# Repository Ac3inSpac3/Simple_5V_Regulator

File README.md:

# Basic 5V Regulator for Raspberry Pi

## Introduction

This 5V regulator was designed for my EGH419 Class (Mechatronics design 3). It was designed to take the high input voltage the main robot ran off, (a 6s Li-Po drone battery or 4 individual 18650 cells in parallel) and output a consistent 5V for the raspberry pi to run off. The regulator needed to be capable of providing enough current for the Pi to run OpenCV object recognition on top of the navigation code. 

## Features

- Input Voltage: 30V (maximum)
- Output Voltage: 5V
- High Current Output

## Schematic
The schematic for this PCB was designed in KiCAD. KiCAD was used because it is a free program and I do not need to mess around with Educational Licences like I did when working in Altium.
A fuse was implemented into the schematic; however, it was not placed when the PCB was assembled.

## PCB
The PCB was designed and sent to JLCPCB to be manufactured (Manufacturing and Gerber files provided).

## Final Product
With the PCB now manufactured it was tested and placed into the robot. It worked well, providing 5V to the Raspberry Pi without any annoying low power warnings like the previous solution had done.

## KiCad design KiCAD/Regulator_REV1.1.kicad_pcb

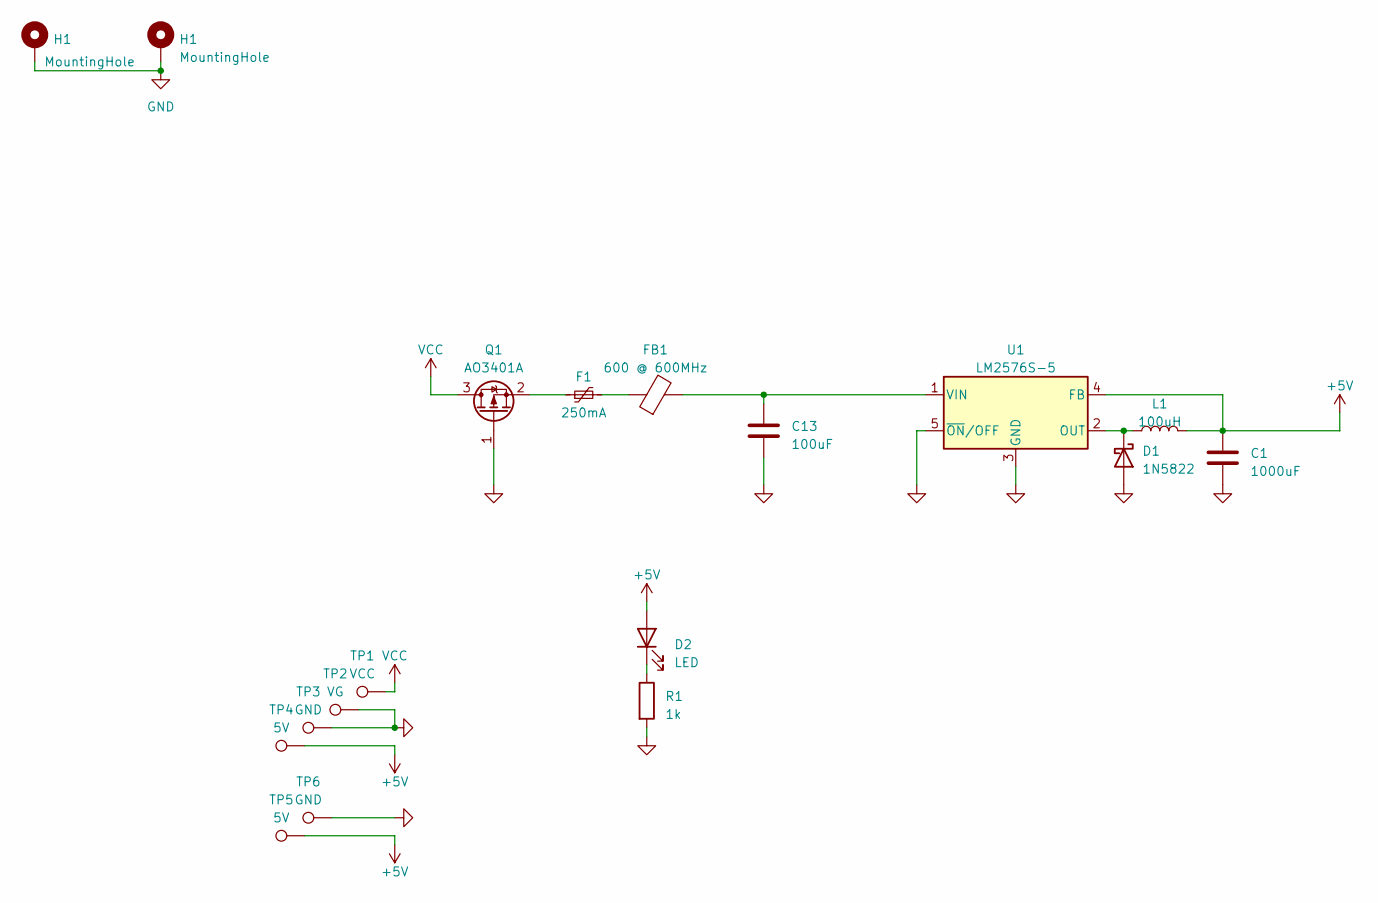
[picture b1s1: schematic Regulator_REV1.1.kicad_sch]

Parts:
C1: 1000uF; C_Elec_10x10.2
C13: 100uF; C_1206_3216Metric
D1: 1N5822; D_DO-201AD_P15.24mm_Horizontal
D2: LED; LED_0603_1608Metric
F1: 250mA; Fuse_1206_3216Metric
FB1: 600 @ 600MHz; L_0805_2012Metric
H1: MountingHole; MountingHole_3.2mm_M3_DIN965_Pad
L1: 100uH; L_Sunlord_MWSA0605S
Q1: AO3401A; SOT-23
R1: 1k; R_0603_1608Metric
TP1: VCC; TestPoint_Pad_2.0x2.0mm
TP2: VG; TestPoint_Pad_2.0x2.0mm
TP3, TP6: GND; TestPoint_Pad_1.0x1.0mm
TP4, TP5: 5V; TestPoint_Pad_1.0x1.0mm
U1: LM2576S-5; TO-263-5_TabPin3

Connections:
+5V: C1.1, D2.2 (A), L1.2, TP4.1, TP5.1, U1.4 (FB)
GND: C1.2, C13.2, D1.2 (A), H1.1, Q1.1 (G), R1.2, TP2.1, TP3.1, TP6.1, U1.3 (GND), U1.5 (~ON/OFF); also elsewhere on the board
unnamed: D1.1 (K), L1.1, U1.2 (OUT)
unnamed: D2.1 (K), R1.1
unnamed: F1.2, FB1.1
unnamed: F1.1, Q1.2 (S)
unnamed: C13.1, FB1.2, U1.1 (VIN)
VCC: Q1.3 (D), TP1.1

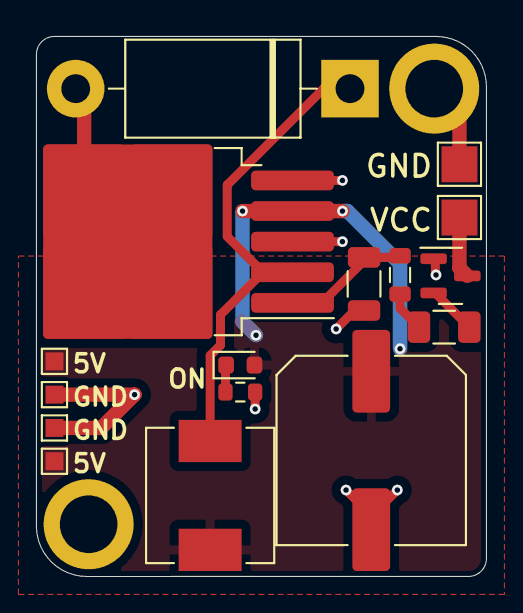
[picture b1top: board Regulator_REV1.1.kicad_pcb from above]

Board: 2 copper layers, 25.0 x 30.0 mm, 18 parts (0 on the bottom side), 8 nets.

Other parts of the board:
H3: MountingHole; MountingHole_3.2mm_M3_DIN965_Pad

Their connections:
GND: H3.1; also elsewhere on the board

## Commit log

2023-06-14 Added KiCAD Files
2024-01-10 Created README.md
2024-01-10 Added Images
